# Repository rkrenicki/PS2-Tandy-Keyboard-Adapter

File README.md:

# PS2 to Tandy 1000 Keyboard Adapter

This is a simple in-line adapter to allow use of more modern PS2 Keyboards on early Tandy 1000 computers.   This adapter works on 1000, 1000A, 1000HD, 1000SX, and 1000TX computers.

## Prerequisites

This adapter is for the Tandy 1000, 1000A, 1000HD, 1000SX, and 1000TX computers only.  It will not work for any other computer model as it is

## Installing

This adapter simply connects in-line between your PS2 keyboard and the Tandy 1000 computer.  Simple plug-and-play.

## Bill of Materials
|Quan |Ref(s)        |Mouser Part Number  |Description                                                     
|-----|--------------|--------------------|----------------------------------------------------------------
| 1   |U1            |556-ATTINY85-20PU   |ATTiny85-20PU Micrcontroller
| 2   |R1, R2        |603-CFR-12JB-52-4K7 |4.7k ohm Resistor
| 1   |R3            |603-CFR-12JB-52-150R|150 ohm Resistor
| 1   |F1            |576-0251001.MRT1L   |1A Polyfuse
| 1   |C1            |594-A101J15C0GF5TAA |100pF Multi Layer Ceramic Capacitor
| 1   |C2            |594-A104M15X7RF5TAA |0.1uF Multi Layer Ceramic Capacitor
| 1   |J1            |806-KMDGX-6S-BS     |MiniDIN 6 Socket

## BIOS

The ATTiny software is written by Scott Baker.

## Built With

* [KiCAD EDA](http://www.kicad-pcb.org/)

## Authors

* **Rob Krenicki** - [rkrenicki](https://github.com/rkrenicki)

## License

Creative Commons Attribution-ShareAlike 4.0 International License (http://creativecommons.org/licenses/by-sa/4.0/)

## Attribution

This board was derrived from works by, uses design elements from, or contains sofware writen by the following:
* Scott Baker (https://www.smbaker.com/tandy-1000-upgrades-ps2-tandy-keyboard-adapter)
* PS/2 Keyboard Library (http://www.nerdkits.com/videos/interrupts_and_ps2_keyboard/)

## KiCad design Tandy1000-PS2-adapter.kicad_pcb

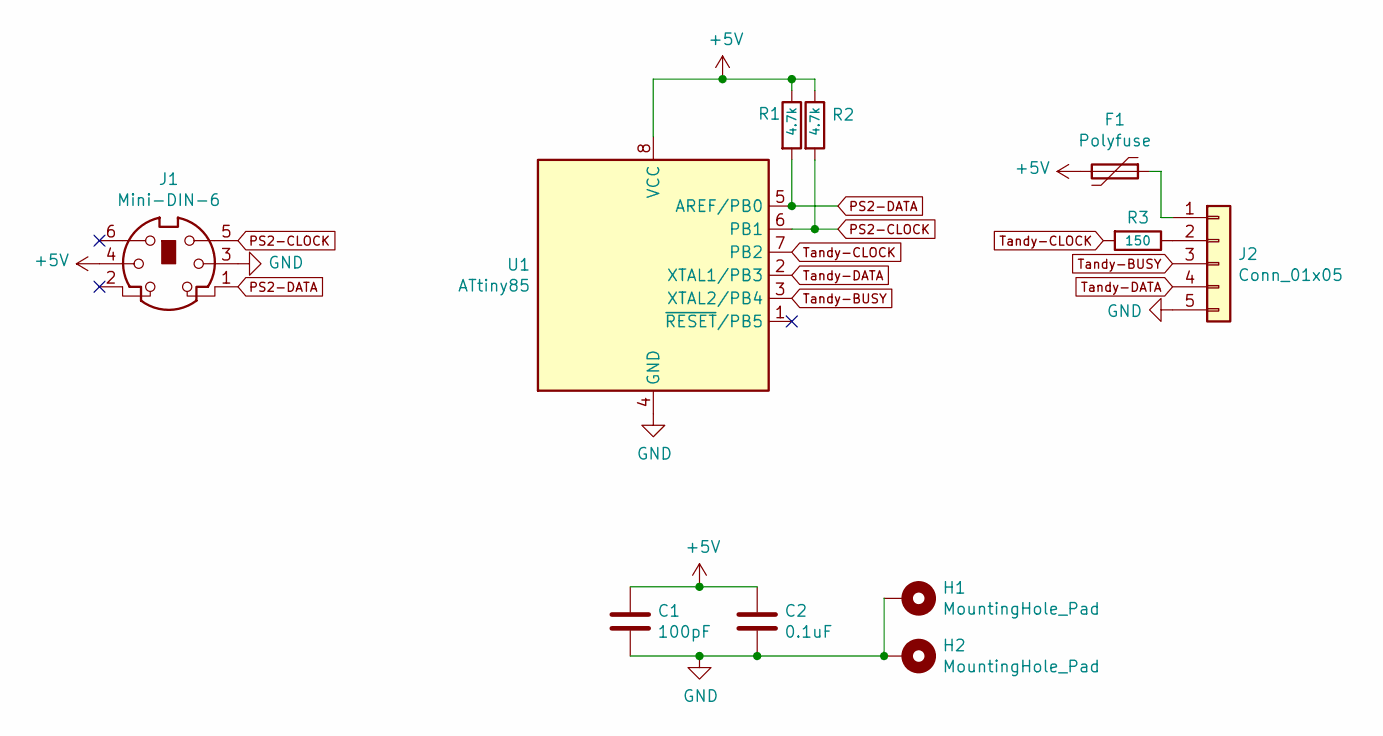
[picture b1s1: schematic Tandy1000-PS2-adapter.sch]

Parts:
C1: 100pF; R_Axial_DIN0204_L3.6mm_D1.6mm_P5.08mm_Horizontal
C2: 0.1uF; R_Axial_DIN0204_L3.6mm_D1.6mm_P5.08mm_Horizontal
F1: Polyfuse; R_Axial_DIN0207_L6.3mm_D2.5mm_P10.16mm_Horizontal
H1, H2: MountingHole_Pad; MountingHole_2.7mm_M2.5_DIN965_Pad
J1: Mini-DIN-6; MINI-DIN-6-FULL-SHIELD
J2: Conn_01x05; PinHeader_1x05_P2.54mm_Vertical
R1, R2: 4.7k; R_Axial_DIN0204_L3.6mm_D1.6mm_P5.08mm_Horizontal
R3: 150; R_Axial_DIN0204_L3.6mm_D1.6mm_P5.08mm_Horizontal
U1: ATtiny85; DIP-8_W7.62mm

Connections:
+5V: C1.1, C2.1, F1.2, J1.4, R1.1, R2.1, U1.8 (VCC)
GND: C1.2, C2.2, H1.1, H2.1, J1.3, J2.5, U1.4 (GND)
unnamed: F1.1, J2.1
unnamed: J2.2, R3.1
PS2-CLOCK: J1.5, R2.2, U1.6 (PB1)
PS2-DATA: J1.1, R1.2, U1.5 (AREF/PB0)
Tandy-BUSY: J2.3, U1.3 (XTAL2/PB4)
Tandy-CLOCK: R3.2, U1.7 (PB2)
Tandy-DATA: J2.4, U1.2 (XTAL1/PB3)

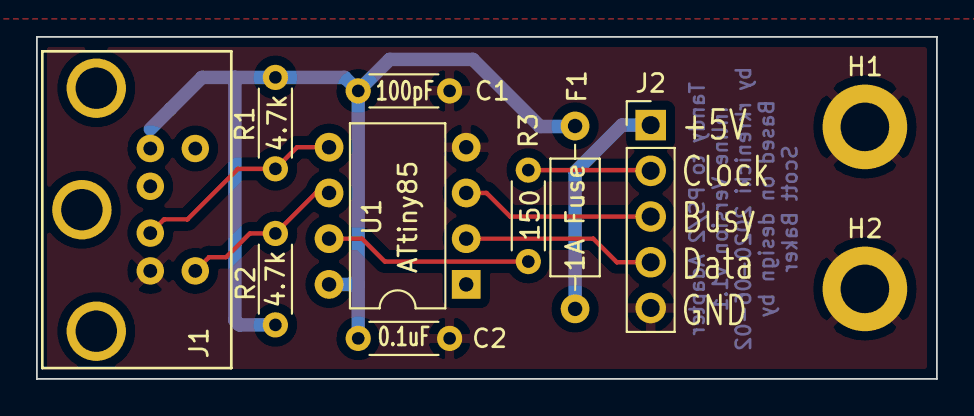
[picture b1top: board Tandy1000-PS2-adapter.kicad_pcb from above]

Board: 2 copper layers, 50.0 x 19.0 mm, 11 parts (0 on the bottom side), 9 nets.

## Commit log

2020-12-17 1.2 Update
    Enlarged mounting holes to 2.7mm for more zip-tie compatibility.
